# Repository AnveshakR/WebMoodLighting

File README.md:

# LED_WEB

A smart LED lighting control system that integrates WS2812B RGB LED strips with Home Assistant for flexible, remote-free control.

## Overview

This project controls a WS2812B RGB LED strip connected to an ESP32 by interfacing with a **Home Assistant** server on the local network. A custom HA integration creates per-ESP entities and a Lovelace dashboard widget for each strip, with no intermediary server required.

### Key Features

- **No Remote Required**: Control lights directly through Home Assistant
- **Easy Scaling**: Adding a new ESP requires only flashing the firmware with a new name and adding one integration entry in HA — no other changes needed
- **Dashboard Widget**: Each ESP gets a native HA color picker and display mode dropdown
- **Real-Time Audio Visualization**: Strip brightness can follow live audio FFT data posted to the ESP's local endpoint

### Available Lighting Modes

- Solid color display
- Breathing color display
- Audio-visualizer color display (requires external audio source posting to `/update_fft`)
- Color spectrum

## Configuration

Create this `env.h` file in the project directory and fill in the values as per your setup.

```cpp
#ifndef ENV_H
#define ENV_H

// WiFi
const char* WIFI_SSID     = "your_wifi_ssid";
const char* WIFI_PASSWORD = "your_wifi_password";

// Home Assistant
const char* HA_HOST  = "http://YOUR_HA_IP:8123";
const char* HA_TOKEN = "your_long_lived_access_token"; // Profile → Long-Lived Access Tokens

// Identity — IMPORTANT: must match the name entered in the LED ESP HA integration
const char* ESP_NAME = "your_esp_name";

// Strip
#define LED_PIN  5      // GPIO pin connected to the LED strip data line
#define NUM_LEDS 300    // total number of LEDs in your strip

#endif
```

## Installation

### 1. Home Assistant Integration

Clone the repo and copy the integration folder into your HA config directory from within the HA Terminal addon:

```bash
git clone https://github.com/AnveshakR/WebMoodLighting.git /tmp/led_web
cp -r /tmp/led_web/custom_components/led_esp /config/custom_components/
rm -rf /tmp/led_web
```

After copying, restart HA:

```bash
ha core restart
```

### 2. Add an ESP in Home Assistant

After restart, go to **Settings → Devices & Services → Add Integration** and search for **LED ESP**. Enter a name for the ESP (e.g. `desk`). This creates three entities:

| Entity | ID | Purpose |
|--------|-----|---------|
| Light | `light.<name>` | RGB color and on/off |
| Select | `select.<name>_display_state` | Display mode dropdown |
| Sensor | `sensor.<name>_ip` | ESP IP address (updated on boot) |

### 3. Flash the ESP32

Make sure `env.h` is configured with the **same name** used in step 2, then flash `led_web.ino` via the Arduino IDE. The ESP should be flashed and started after the integration entry exists in HA, since it posts its IP to HA on boot.

### 4. Lovelace Dashboard

Add a **Light card** pointing at `light.<name>` for the color picker, and an **Entities card** or **Tile card** with `select.<name>_display_state` below it. Suggested YAML for a single ESP named `test_lights`:

```yaml
- type: entities
  title: Test Lights LED Strip
  entities:
    - entity: light.test_lights
      name: Color & Power
    - entity: select.test_lights_display_state
      name: Display Mode
    - entity: sensor.test_lights_ip
      name: IP
      icon: mdi:ip-network
```

## 3D Printed Enclosure

The [3D print files](3D%20print%20files/) folder contains STL files for a custom enclosure to house the ESP32 and wire connections. View them interactively on GitHub: [Box](3D%20print%20files/esp%20box.STL) · [Lid](3D%20print%20files/esp%20box%20lid.STL)

### Required Components

1. **USB-C Connector**: [USB-C Panel Mount Cable](https://a.co/d/ibNtGKY)
2. **WAGO Lever Nut Connectors**: [3-conductor lever nuts × 3](https://a.co/d/3chznWW)
3. **ESP32 Board**: [ESP32 DOIT DevKit V1](https://a.co/d/75TbzBZ)
4. **LED Strip**: [WS2812B LED Strip](https://a.co/d/dlXuyIC)
5. **M3×8 Screws**: 4× screws to secure the ESP32 to the box

### Wiring Connections

Use the three WAGO lever nut connectors to make the following connections:

**Connector 1 (Power +):**
- VIN pin of ESP32
- Positive (+) wire of USB-C connector
- Positive (+) wire of LED strip

**Connector 2 (Ground -):**
- GND pin of ESP32
- Negative (-) wire of USB-C connector
- Negative (-) wire of LED strip

**Connector 3 (Data Signal):**
- Data/TRIG pin of LED strip
- GPIO pin of ESP32 (as defined by `LED_PIN` in env.h, recommended: GPIO 5)

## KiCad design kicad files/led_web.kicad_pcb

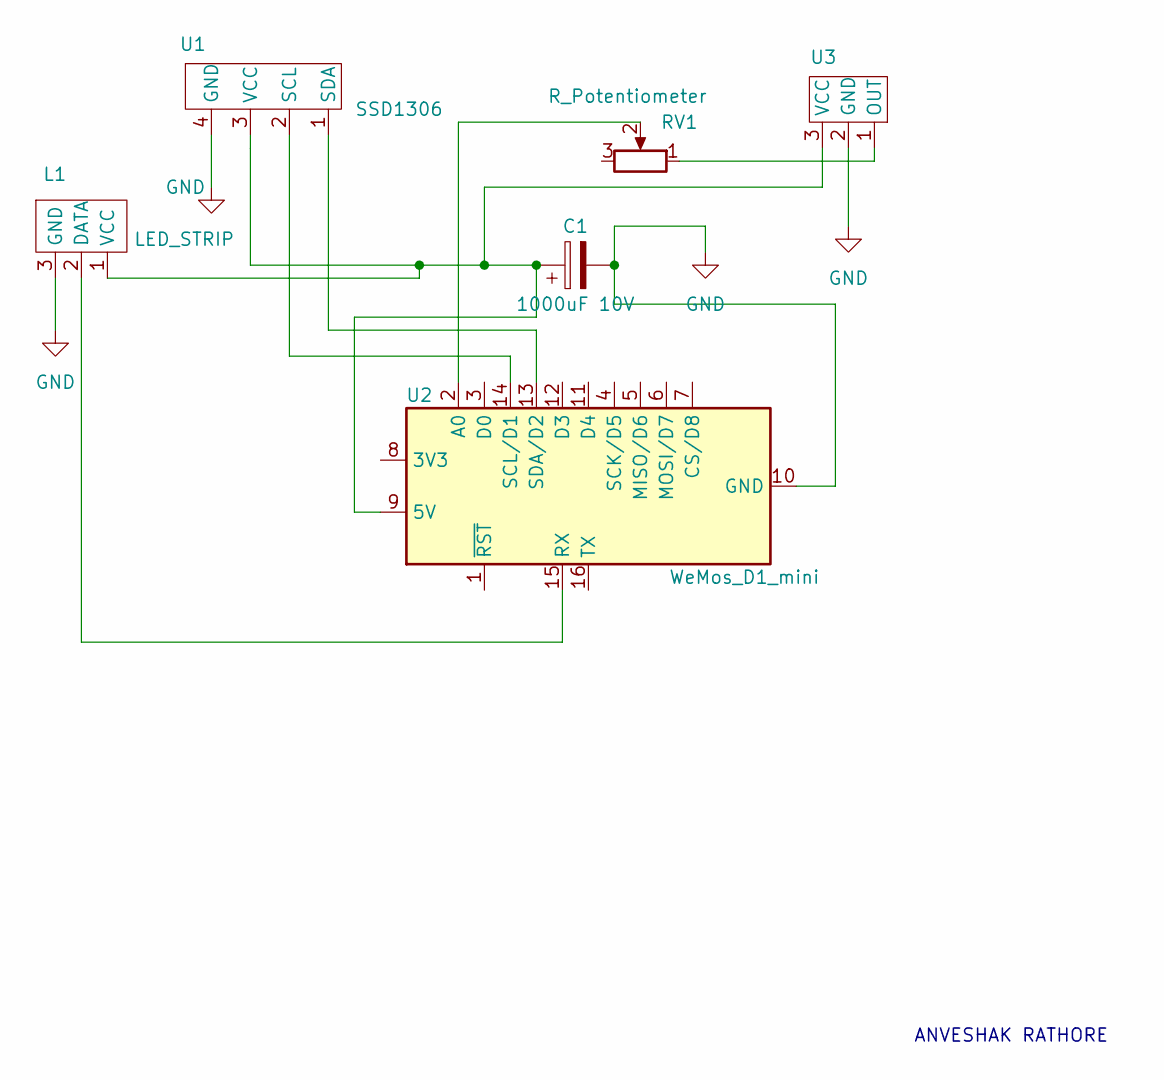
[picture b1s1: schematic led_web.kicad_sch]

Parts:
C1: 1000uF 10V; CP_Radial_D5.0mm_P2.50mm
L1: LED_STRIP
RV1: R_Potentiometer; Potentiometer_Runtron_RM-065_Vertical
U1: SSD1306
U2: WeMos_D1_mini; WEMOS_D1_mini_light
U3: (no value)

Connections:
GND: C1.2, L1.3 (GND), U1.4 (GND), U2.10 (GND), U3.2 (GND)
unnamed: C1.1, L1.1 (VCC), U1.3 (VCC), U2.9 (5V), U3.3 (VCC)
unnamed: L1.2 (DATA), U2.15 (RX)
unnamed: RV1.1, U3.1 (OUT)
unnamed: RV1.2, U2.2 (A0)
unnamed: U1.1 (SDA), U2.13 (SDA/D2)
unnamed: U1.2 (SCL), U2.14 (SCL/D1)

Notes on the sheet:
ANVESHAK RATHORE

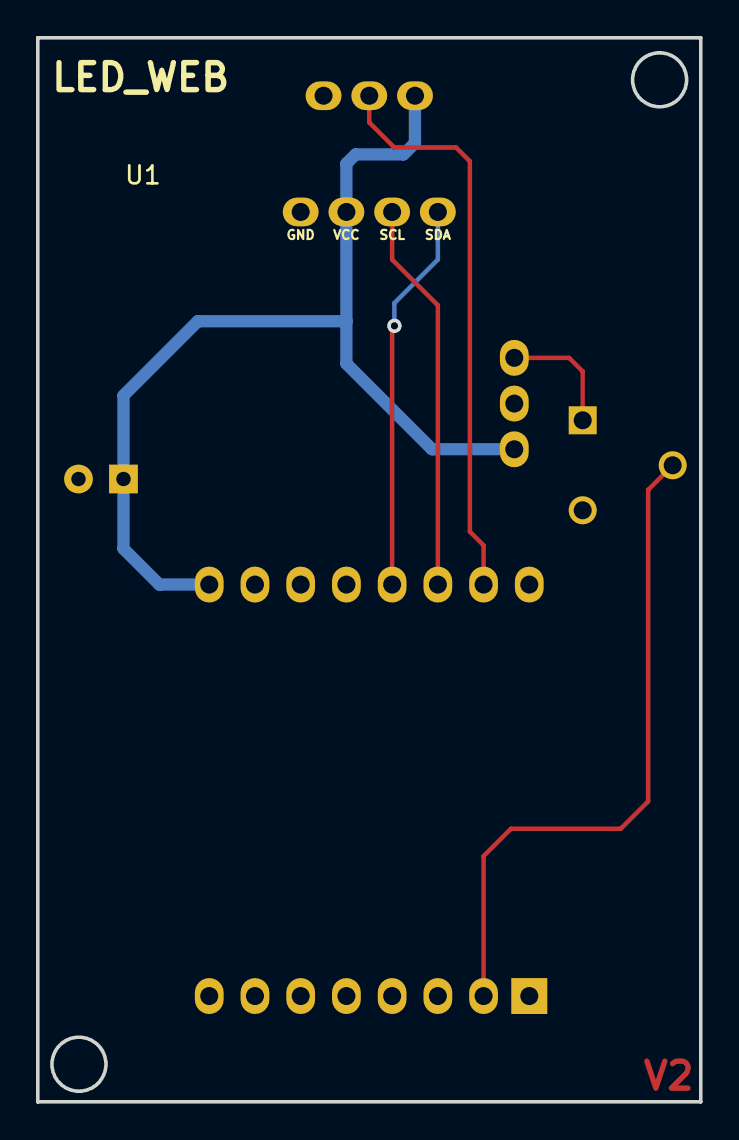
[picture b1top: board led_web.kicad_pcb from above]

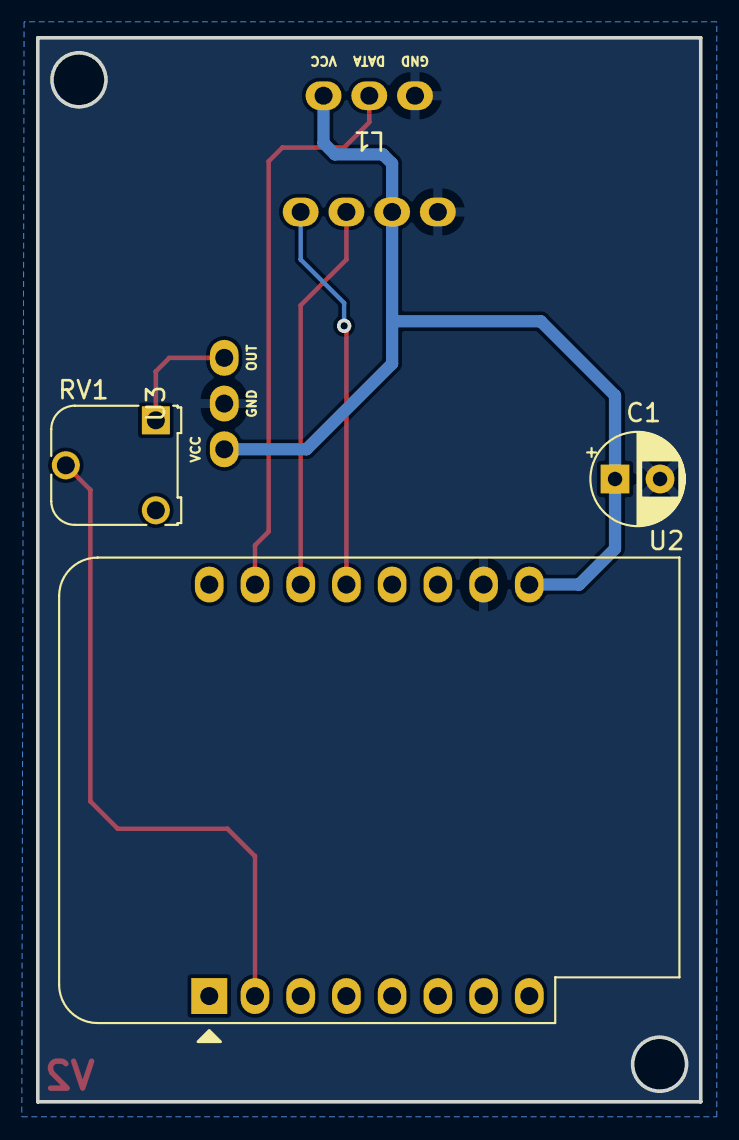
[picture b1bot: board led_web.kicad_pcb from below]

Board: 2 copper layers, 36.8 x 59.1 mm, 6 parts (5 on the bottom side), 7 nets.

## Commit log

2022-01-01 new webpage, hardcoded breathe
2022-01-08 added SSD1306 functionality
2022-01-11 OTA uploading + config file
2022-01-17 removed first led flickering by using NPB
2022-04-11 i forgot pushing to github lol
2022-06-02 added kicad files
2022-08-16 pcb redesign
2022-08-16 added readme
2022-11-10 color and mode independent + RGB spectrum mode
2022-11-10 comments
2024-03-18 updated README, added requirements.txt
2024-09-01 added support for AnveshakR/discord-PA
2024-12-07 christmas lights setting ^^
2025-07-16 initial commit?
2025-07-18 added webapp files to interact with local HA
2025-07-18 forgot to add html lol
2026-01-03 added 3d model files, and some refactoring in the ino files
2026-01-03 slight tolerance issues in the esp box dimensions, fixed
2026-03-09 replaced Flask webapp with native HA integration, updated README and cleaned up comments
2026-03-09 added fft streamer script, updated for new HA entity IDs
